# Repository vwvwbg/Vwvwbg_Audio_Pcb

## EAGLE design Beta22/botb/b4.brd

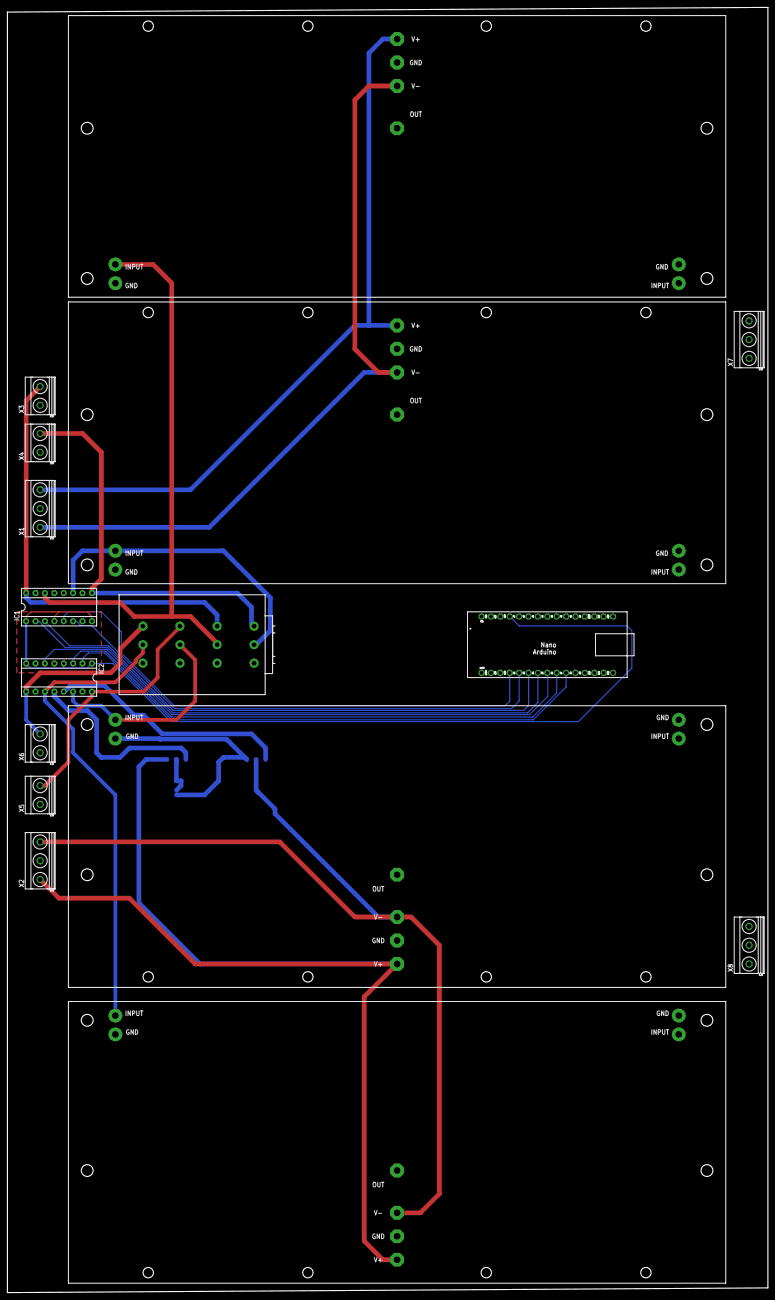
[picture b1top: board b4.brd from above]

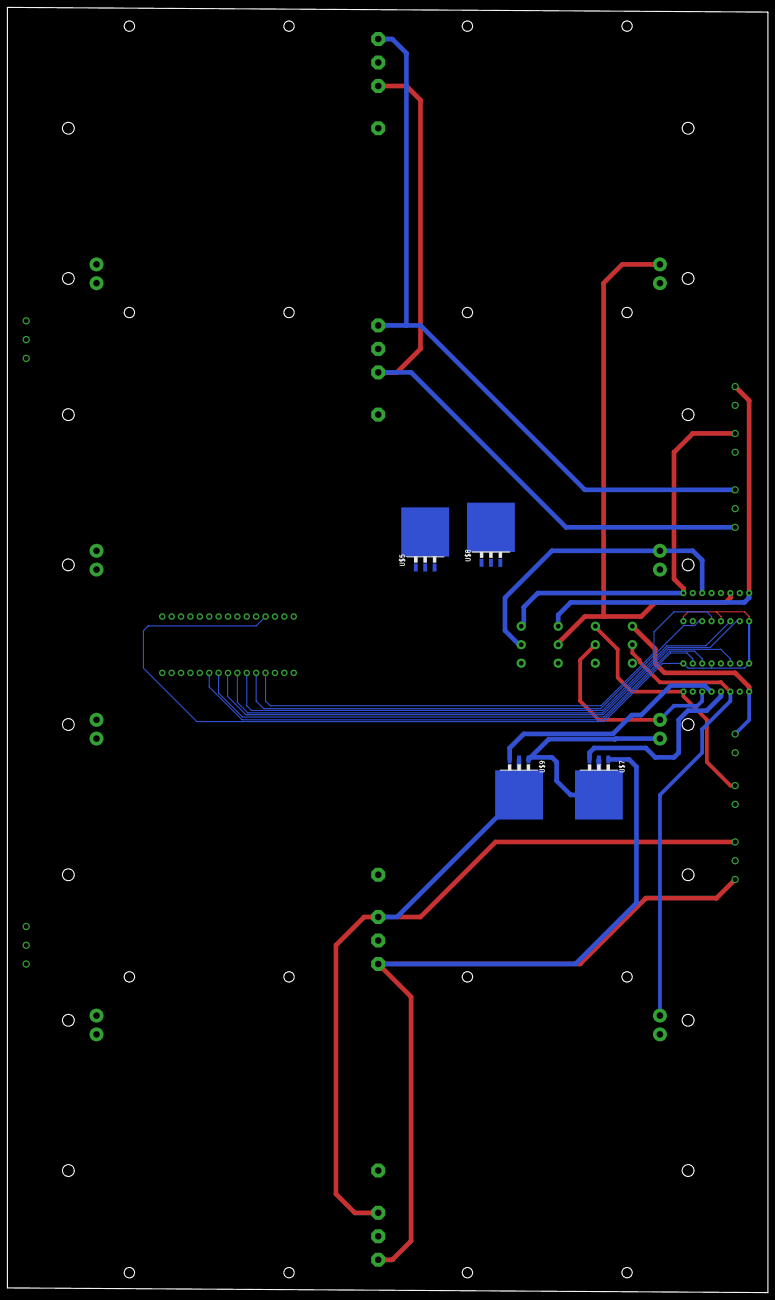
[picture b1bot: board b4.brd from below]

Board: 2 copper layers, 205.7 x 347.6 mm, 20 parts (4 on the bottom side), 25 nets.

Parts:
IC1, IC2: PGA2311P; DIL16
PCB1: ARDUINO_NANO
U$1, U$2, U$3, U$4: B22
U$5, U$7: MC78XX; TO263-3
U$6: ALPSRK274; RK274
U$8, U$9: MC79XX; TO263-3
X1, X2, X7, X8: MKDSN1,5/3-5,08
X3, X4, X5, X6: MKDSN1,5/2-5,08

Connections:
DGND: IC1.5, IC2.5, PCB1.GND
GND: IC1.10, IC1.15, IC2.10, IC2.15, U$1.GND, U$1.GND1, U$1.GND2, U$2.GND, U$2.GND1, U$2.GND2, U$3.GND, U$3.GND1, U$3.GND2, U$4.GND, U$4.GND1, U$4.GND2, U$5.2, U$5.TAB, U$6.G1, U$6.G2, U$6.G3, U$6.G4, U$7.2, U$7.TAB, U$8.1, U$9.1, X1.2, X2.2, X3.1, X5.1, X6.1, X7.2, X8.2
unnamed: U$3.V+, U$4.V+, U$5.1, X1.3, X7.3
unnamed: U$3.V-, U$4.V-, U$8.2, U$8.TAB, X1.1, X7.1
unnamed: IC1.16, U$6.I2, X3.2
unnamed: U$1.V+, U$2.V+, U$7.1, X2.1, X8.1
unnamed: U$1.V-, U$2.V-, U$9.2, U$9.TAB, X2.3, X8.3
unnamed: IC1.14, U$4.IN1, U$6.O2
unnamed: IC1.9, U$6.I1, X4.2
unnamed: IC1.11, U$3.IN1, U$6.O1
unnamed: IC2.14, U$2.IN2, U$6.O3
unnamed: IC2.11, U$1.IN2, U$6.O4
unnamed: IC2.9, U$6.I4, X6.2
unnamed: IC1.2, PCB1.D4
unnamed: IC2.16, U$6.I3, X5.2
unnamed: IC1.3, PCB1.D3
unnamed: IC2.2, PCB1.D7
unnamed: IC2.3, PCB1.D6
unnamed: IC1.1, IC1.4, IC1.8, IC2.1, IC2.4, IC2.8, PCB1.5V
unnamed: IC2.13, U$9.3
unnamed: IC2.6, PCB1.D5
unnamed: IC1.6, PCB1.D2
unnamed: IC2.12, U$7.3
unnamed: IC1.12, U$5.3
unnamed: IC1.13, U$8.3

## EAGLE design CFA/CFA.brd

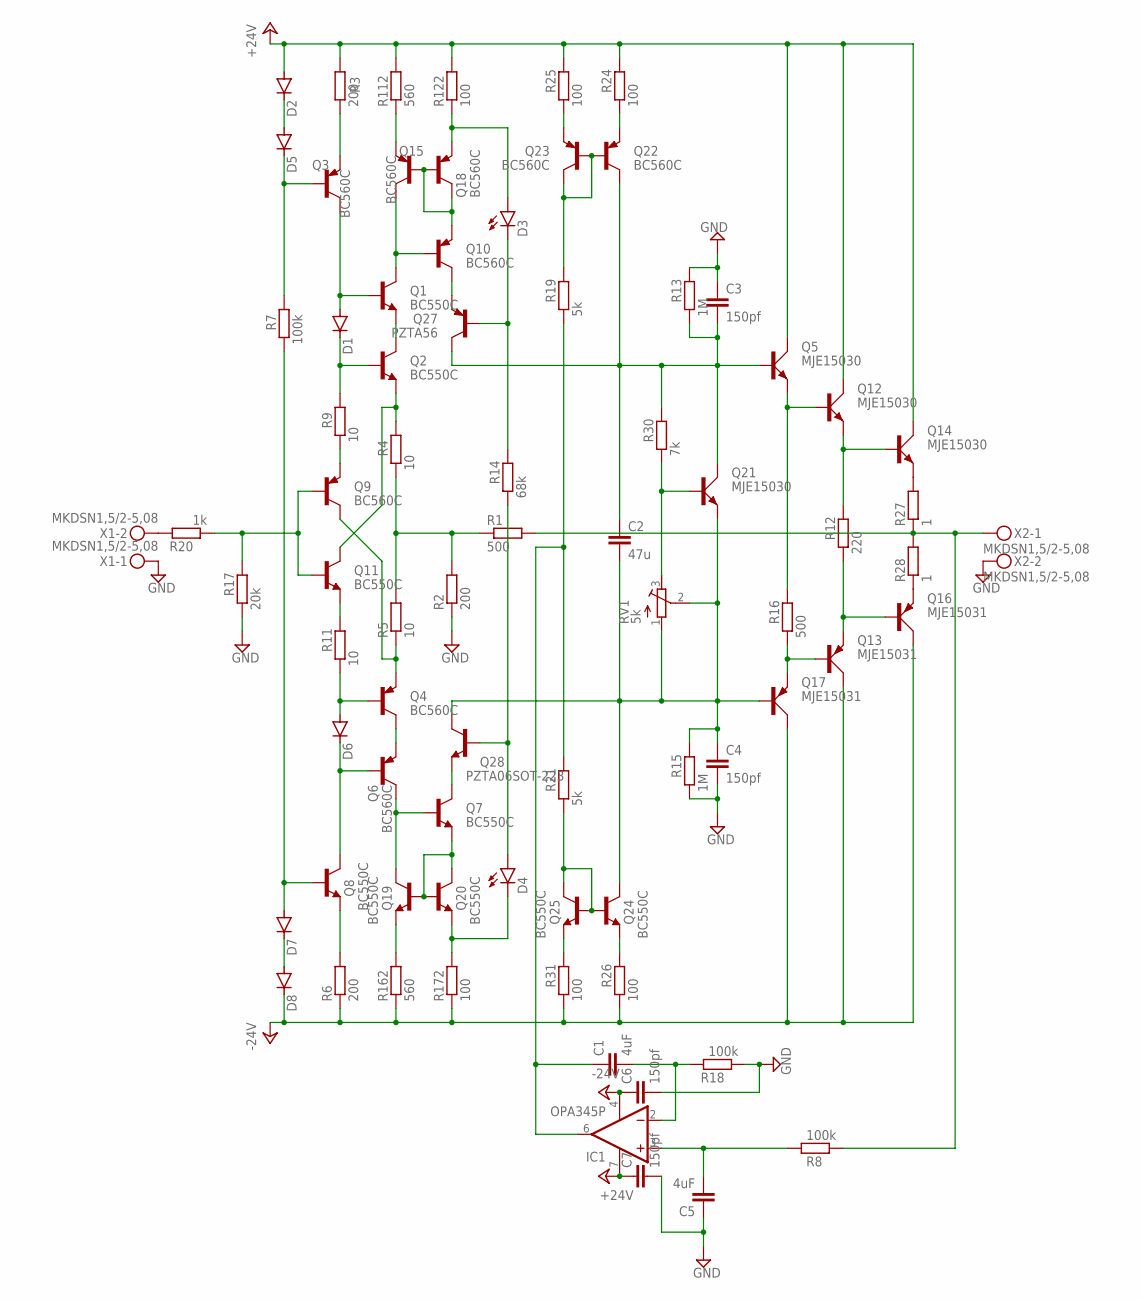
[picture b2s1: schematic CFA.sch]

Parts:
C1, C5: 4uF; C1210
C2: 47u; C1210
C3, C4, C6, C7: 150pf; C0805
D1, D2, D5, D6, D7, D8: DIODE-SOD80C; SOD80C
D3, D4: LED5MM
IC1: OPA345P; DIL08
Q1, Q2, Q7, Q8, Q11, Q19, Q20, Q24, Q25: BC550C; TO92-EBC
Q3, Q4, Q6, Q9, Q10, Q15, Q18, Q22, Q23: BC560C; TO92-EBC
Q5, Q12, Q14, Q21: MJE15030; TO220AV
Q13, Q16, Q17: MJE15031; TO220AV
Q27: PZTA56; SOT223
Q28: PZTA06SOT-223; SOT223
R1, R16: 500; MINI_MELF-0204R
R2, R3, R6: 200; MINI_MELF-0204R
R4, R5, R9, R11: 10; MINI_MELF-0204R
R7, R8, R18: 100k; MINI_MELF-0204R
R12: 220; MINI_MELF-0204R
R13, R15: 1M; MINI_MELF-0204R
R14: 68k; MINI_MELF-0204R
R17: 20k; MINI_MELF-0204R
R19, R21: 5k; MINI_MELF-0204R
R20: 1k; MINI_MELF-0204R
R24, R25, R26, R31, R122, R172: 100; MINI_MELF-0204R
R27, R28: 1; 0617/22
R30: 7k; MINI_MELF-0204R
R112, R162: 560; MINI_MELF-0204R
RV1: 5k; RTRIM3296W
X1, X2: MKDSN1,5/2-5,08

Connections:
+24V: C7.1, D2.A, IC1.7 (V+), Q5.C, Q12.C, Q14.C, R3.2, R24.2, R25.2, R112.2, R122.2
-24V: C6.1, D8.C, IC1.4 (V-), Q13.C, Q16.C, Q17.C, R6.1, R26.1, R31.1, R162.1, R172.1
GND: C3.1, C4.2, C5.1, C6.2, C7.2, R2.1, R13.2, R15.1, R17.1, R18.1, X1.1, X2.2
unnamed: Q21.B, R30.1, RV1.3 (E)
unnamed: Q3.E, R3.1
unnamed: D1.A, Q1.B, Q3.C
unnamed: D2.C, D5.A
unnamed: D5.C, Q3.B, R7.2
unnamed: D1.C, Q2.B, R9.2
unnamed: Q1.E, Q2.C
unnamed: Q2.E, Q11.C, R4.2
unnamed: R1.1, R2.2, R4.1, R5.2
unnamed: Q4.E, Q9.C, R5.1
unnamed: Q4.C, Q6.E
unnamed: D6.A, Q4.B, R11.1
unnamed: D6.C, Q6.B, Q8.C
unnamed: Q8.E, R6.2
unnamed: D7.A, Q8.B, R7.1
unnamed: D7.C, D8.A
unnamed: R20.2, X1.2
unnamed: Q9.E, R9.1
unnamed: Q11.E, R11.2
unnamed: Q15.E, R112.1
unnamed: Q9.B, Q11.B, R17.2, R20.1
unnamed: Q1.C, Q10.B, Q15.C
unnamed: Q10.E, Q15.B, Q18.B, Q18.C
unnamed: D3.A, Q18.E, R122.1
unnamed: Q10.C, Q27.3 (E)
unnamed: D3.K (C), Q27.1 (B), R14.2
unnamed: Q7.E, Q19.B, Q20.B, Q20.C
unnamed: D4.K (C), Q20.E, R172.2
unnamed: Q19.E, R162.2
unnamed: Q6.C, Q7.B, Q19.C
unnamed: Q7.C, Q28.3 (E)
unnamed: D4.A, Q28.1 (B), R14.1
unnamed: Q12.E, Q14.B, R12.2
unnamed: C2.1, C3.2, Q5.B, Q21.C, Q22.C, Q27.2 (C), Q27.4 (C), R13.1, R30.2
unnamed: Q22.B, Q23.B, Q23.C, R19.2
unnamed: Q24.B, Q25.B, Q25.C, R21.1
unnamed: Q23.E, R25.1
unnamed: Q22.E, R24.1
unnamed: C1.1, IC1.6 (OUT), R19.1, R21.2
unnamed: R1.2, R8.1, R27.1, R28.2, X2.1
unnamed: Q25.E, R31.2
unnamed: Q24.E, R26.2
unnamed: Q5.E, Q12.B, R16.2
unnamed: Q13.B, Q17.E, R16.1
unnamed: C2.2, C4.1, Q17.B, Q21.E, Q24.C, Q28.2 (C), Q28.4 (C), R15.2, RV1.1 (A), RV1.2 (S)
unnamed: Q13.E, Q16.B, R12.1
unnamed: Q14.E, R27.2
unnamed: Q16.E, R28.1
unnamed: C1.2, IC1.2 (-IN), R18.2
unnamed: C5.2, IC1.3 (+IN), R8.2

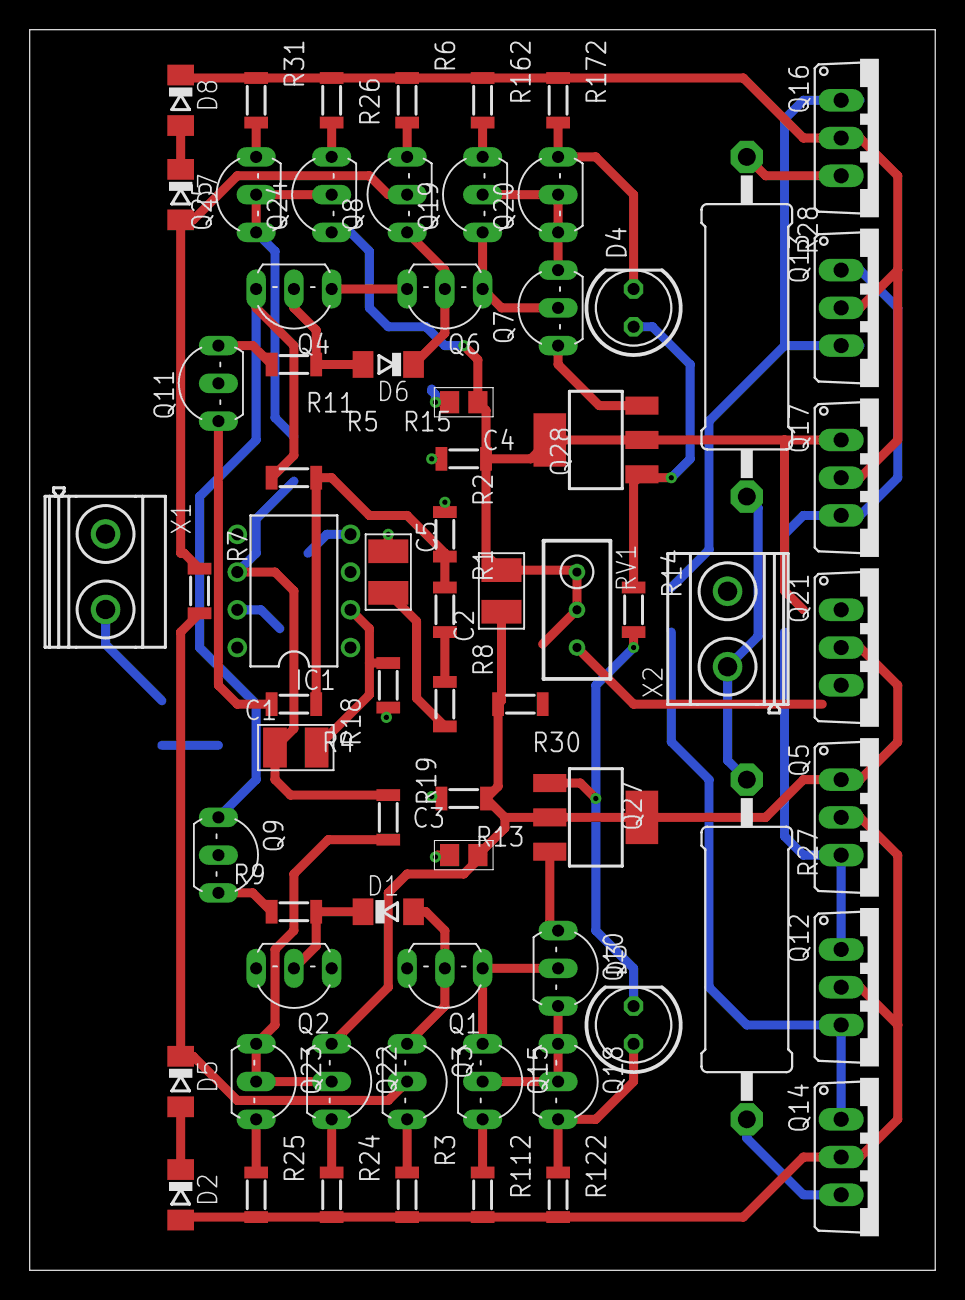
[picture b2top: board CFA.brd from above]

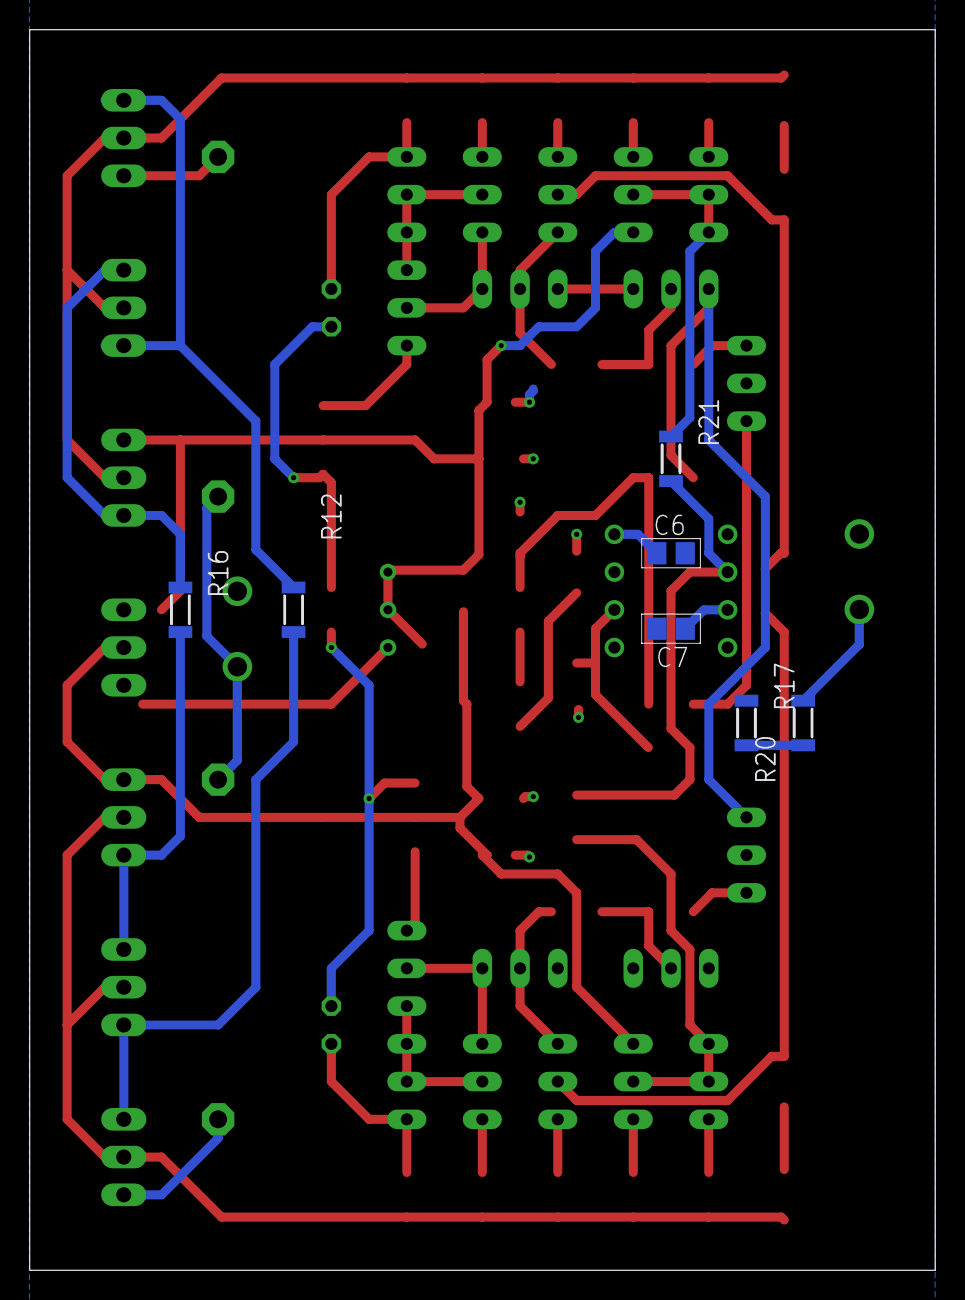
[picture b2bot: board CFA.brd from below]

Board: 2 copper layers, 60.9 x 83.5 mm, 77 parts (7 on the bottom side), 53 nets.

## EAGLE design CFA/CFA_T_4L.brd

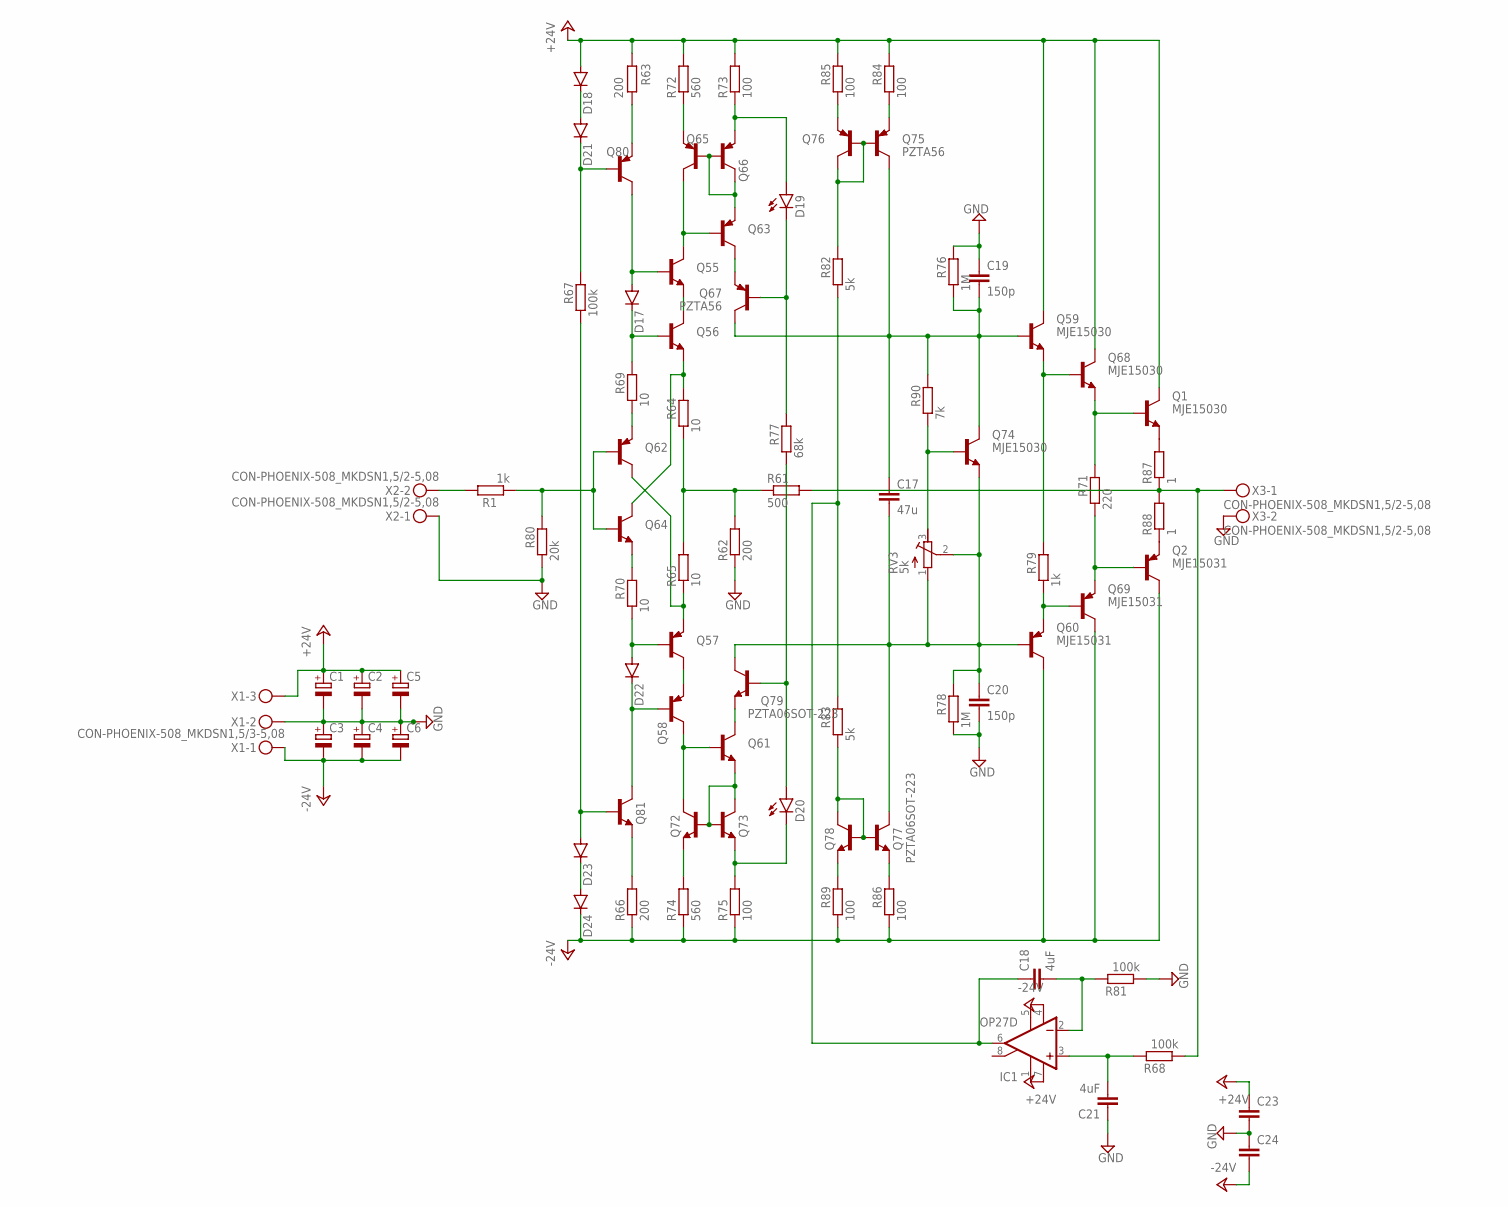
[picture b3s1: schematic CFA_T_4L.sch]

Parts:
C1, C2, C3, C4, C5, C6: CPOL-EUE3.5-8; E3,5-8
C17: 47u; C1210
C18, C21: 4uF; C1210
C19, C20: 150p; C0805
C23, C24: C-EUC0603K; C0603K
D17, D18, D21, D22, D23, D24: DIODE-SOD80C; SOD80C
D19, D20: LED3MM
IC1: OP27D; SO08
Q1, Q59, Q68, Q74: MJE15030; TRANSISTOR_TO220KG
Q2, Q60, Q69: MJE15031; TRANSISTOR_TO220KG
Q55, Q56, Q64, Q72, Q73, Q78, Q81: TRANSISTOR_BC850-NPN-SOT23-BEC; TRANSISTOR_SOT23-BEC
Q57, Q58, Q62, Q63, Q65, Q66, Q76, Q80: TRANSISTOR_BC857C-PNP-SOT23-BEC; TRANSISTOR_SOT23-BEC
Q61: TRANSISTOR_BC847-NPN-SOT23-BEC; TRANSISTOR_SOT23-BEC
Q67, Q75: PZTA56; SOT223
Q77, Q79: PZTA06SOT-223; SOT223
R1, R79: 1k; MINI_MELF-0204W
R61: 500; MINI_MELF-0204W
R62, R63, R66: 200; MINI_MELF-0204W
R64, R65, R69, R70: 10; MINI_MELF-0204W
R67, R68, R81: 100k; MINI_MELF-0204W
R71: 220; MINI_MELF-0204W
R72, R74: 560; MINI_MELF-0204W
R73, R75, R84, R85, R86, R89: 100; MINI_MELF-0204W
R76, R78: 1M; MINI_MELF-0204W
R77: 68k; MINI_MELF-0204W
R80: 20k; MINI_MELF-0204W
R82, R83: 5k; MINI_MELF-0204W
R87, R88: 1; TO220-2
R90: 7k; MINI_MELF-0204W
RV3: 5k; RTRIM3296W
X1: CON-PHOENIX-508_MKDSN1,5/3-5,08
X2, X3: CON-PHOENIX-508_MKDSN1,5/2-5,08

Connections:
+24V: C1.+, C2.+, C5.+, C23.1, D18.A, IC1.7 (V+), Q1.2 (C), Q59.2 (C), Q68.2 (C), R63.2, R72.2, R73.2, R84.2, R85.2, X1.3
-24V: C3.-, C4.-, C6.-, C24.2, D24.C, IC1.4 (V-), Q2.2 (C), Q60.2 (C), Q69.2 (C), R66.1, R74.1, R75.1, R86.1, R89.1, X1.1
GND: C1.-, C2.-, C3.+, C4.+, C5.-, C6.+, C19.1, C20.2, C21.1, C23.2, C24.1, R62.1, R76.2, R78.1, R80.1, R81.1, X1.2, X2.1, X3.2
unnamed: C17.2, C20.1, Q60.1 (B), Q74.3 (E), Q77.2 (C), Q77.4 (C), Q79.2 (C), Q79.4 (C), R78.2, RV3.1 (A), RV3.2 (S)
unnamed: Q74.1 (B), R90.1, RV3.3 (E)
unnamed: R1.2, X2.2
unnamed: Q1.3 (E), R87.2
unnamed: Q2.3 (E), R88.1
unnamed: Q80.E, R63.1
unnamed: D17.A, Q55.B, Q80.C
unnamed: D18.C, D21.A
unnamed: D21.C, Q80.B, R67.2
unnamed: D17.C, Q56.B, R69.2
unnamed: Q55.E, Q56.C
unnamed: Q56.E, Q64.C, R64.2
unnamed: R61.1, R62.2, R64.1, R65.2
unnamed: Q57.E, Q62.C, R65.1
unnamed: D22.A, Q57.B, R70.1
unnamed: D22.C, Q58.B, Q81.C
unnamed: Q81.E, R66.2
unnamed: D23.C, D24.A
unnamed: Q57.C, Q58.E
unnamed: Q62.E, R69.1
unnamed: Q64.E, R70.2
unnamed: Q62.B, Q64.B, R1.1, R80.2
unnamed: Q55.C, Q63.B, Q65.C
unnamed: Q63.E, Q65.B, Q66.B, Q66.C
unnamed: Q65.E, R72.1
unnamed: D19.A, Q66.E, R73.1
unnamed: Q63.C, Q67.3 (E)
unnamed: D19.K (C), Q67.1 (B), R77.2
unnamed: Q61.E, Q72.B, Q73.B, Q73.C
unnamed: D20.K (C), Q73.E, R75.2
unnamed: Q72.E, R74.2
unnamed: Q58.C, Q61.B, Q72.C
unnamed: Q61.C, Q79.3 (E)
unnamed: D20.A, Q79.1 (B), R77.1
unnamed: C17.1, C19.2, Q59.1 (B), Q67.2 (C), Q67.4 (C), Q74.2 (C), Q75.2 (C), Q75.4 (C), R76.1, R90.2
unnamed: Q75.1 (B), Q76.B, Q76.C, R82.2
unnamed: Q77.1 (B), Q78.B, Q78.C, R83.1
unnamed: Q76.E, R85.1
unnamed: Q75.3 (E), R84.1
unnamed: R61.2, R68.1, R87.1, R88.2, X3.1
unnamed: Q78.E, R89.2
unnamed: Q77.3 (E), R86.2
unnamed: Q59.3 (E), Q68.1 (B), R79.2
unnamed: Q60.3 (E), Q69.1 (B), R79.1
unnamed: Q1.1 (B), Q68.3 (E), R71.2
unnamed: Q2.1 (B), Q69.3 (E), R71.1
unnamed: C18.2, IC1.2 (-IN), R81.2
unnamed: C21.2, IC1.3 (+IN), R68.2
unnamed: D23.A, Q81.B, R67.1
unnamed: C18.1, IC1.6 (OUT), R82.1, R83.2

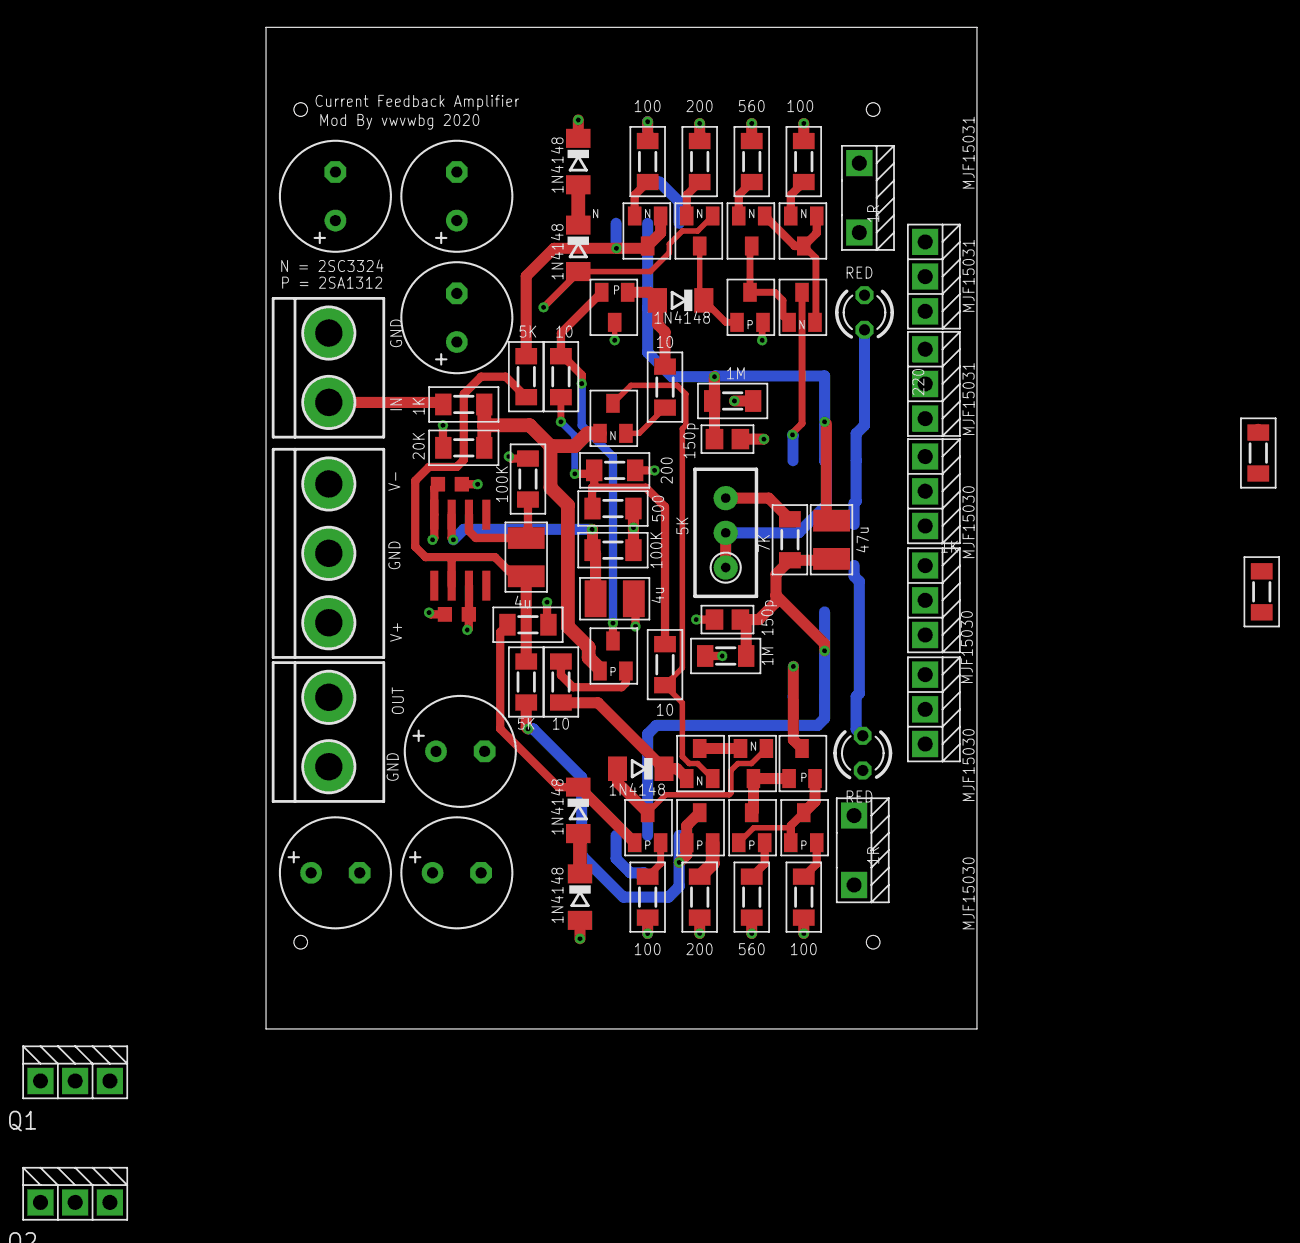
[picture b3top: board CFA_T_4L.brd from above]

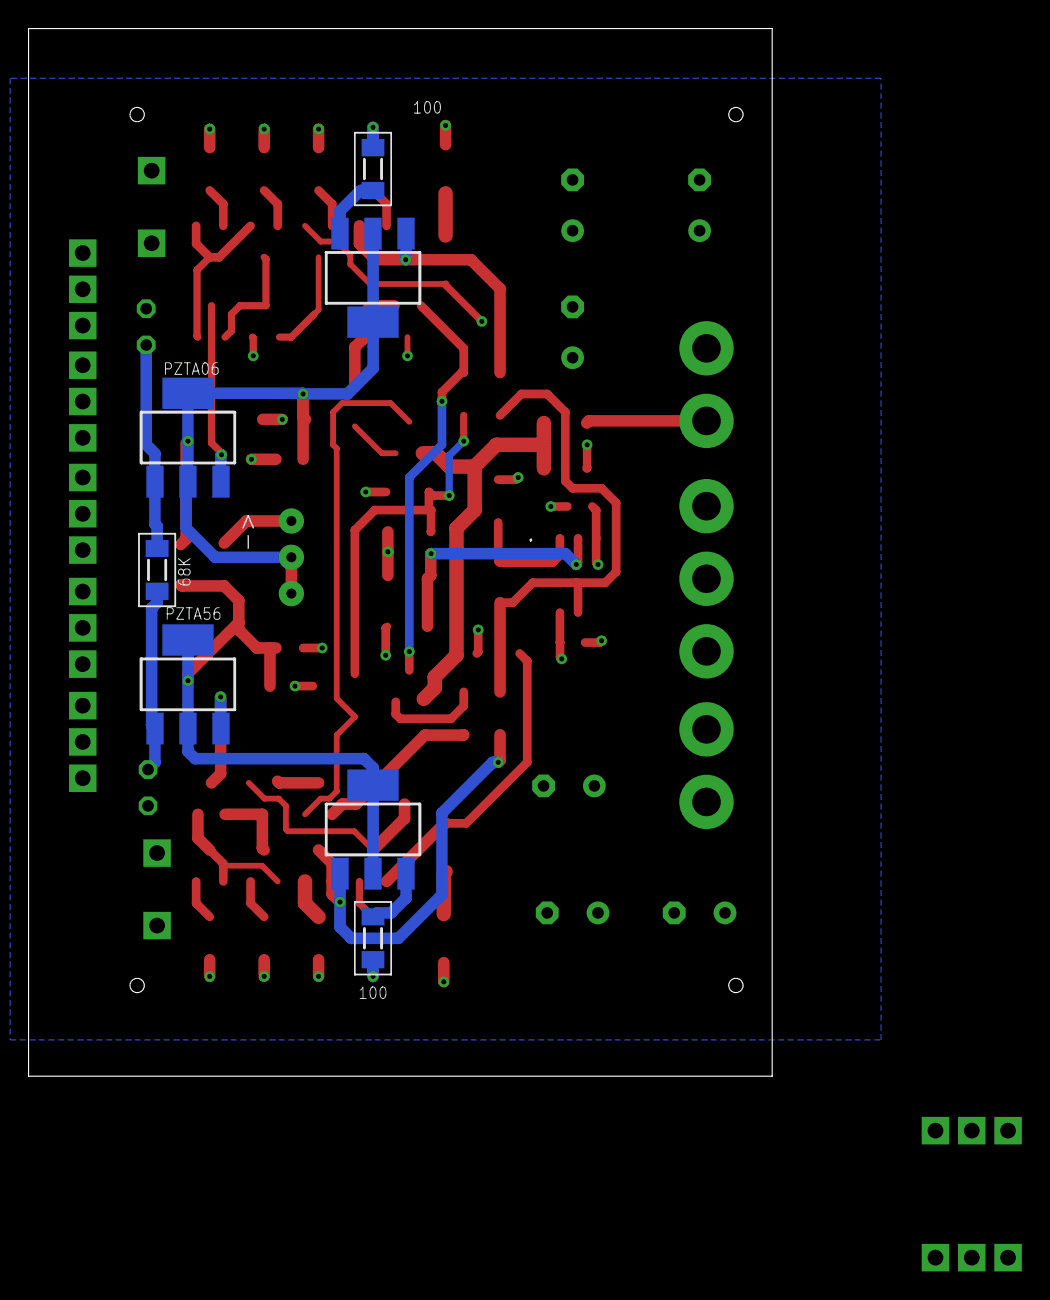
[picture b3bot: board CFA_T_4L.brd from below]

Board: 4 copper layers, 52.0 x 73.3 mm, 84 parts (7 on the bottom side), 53 nets.

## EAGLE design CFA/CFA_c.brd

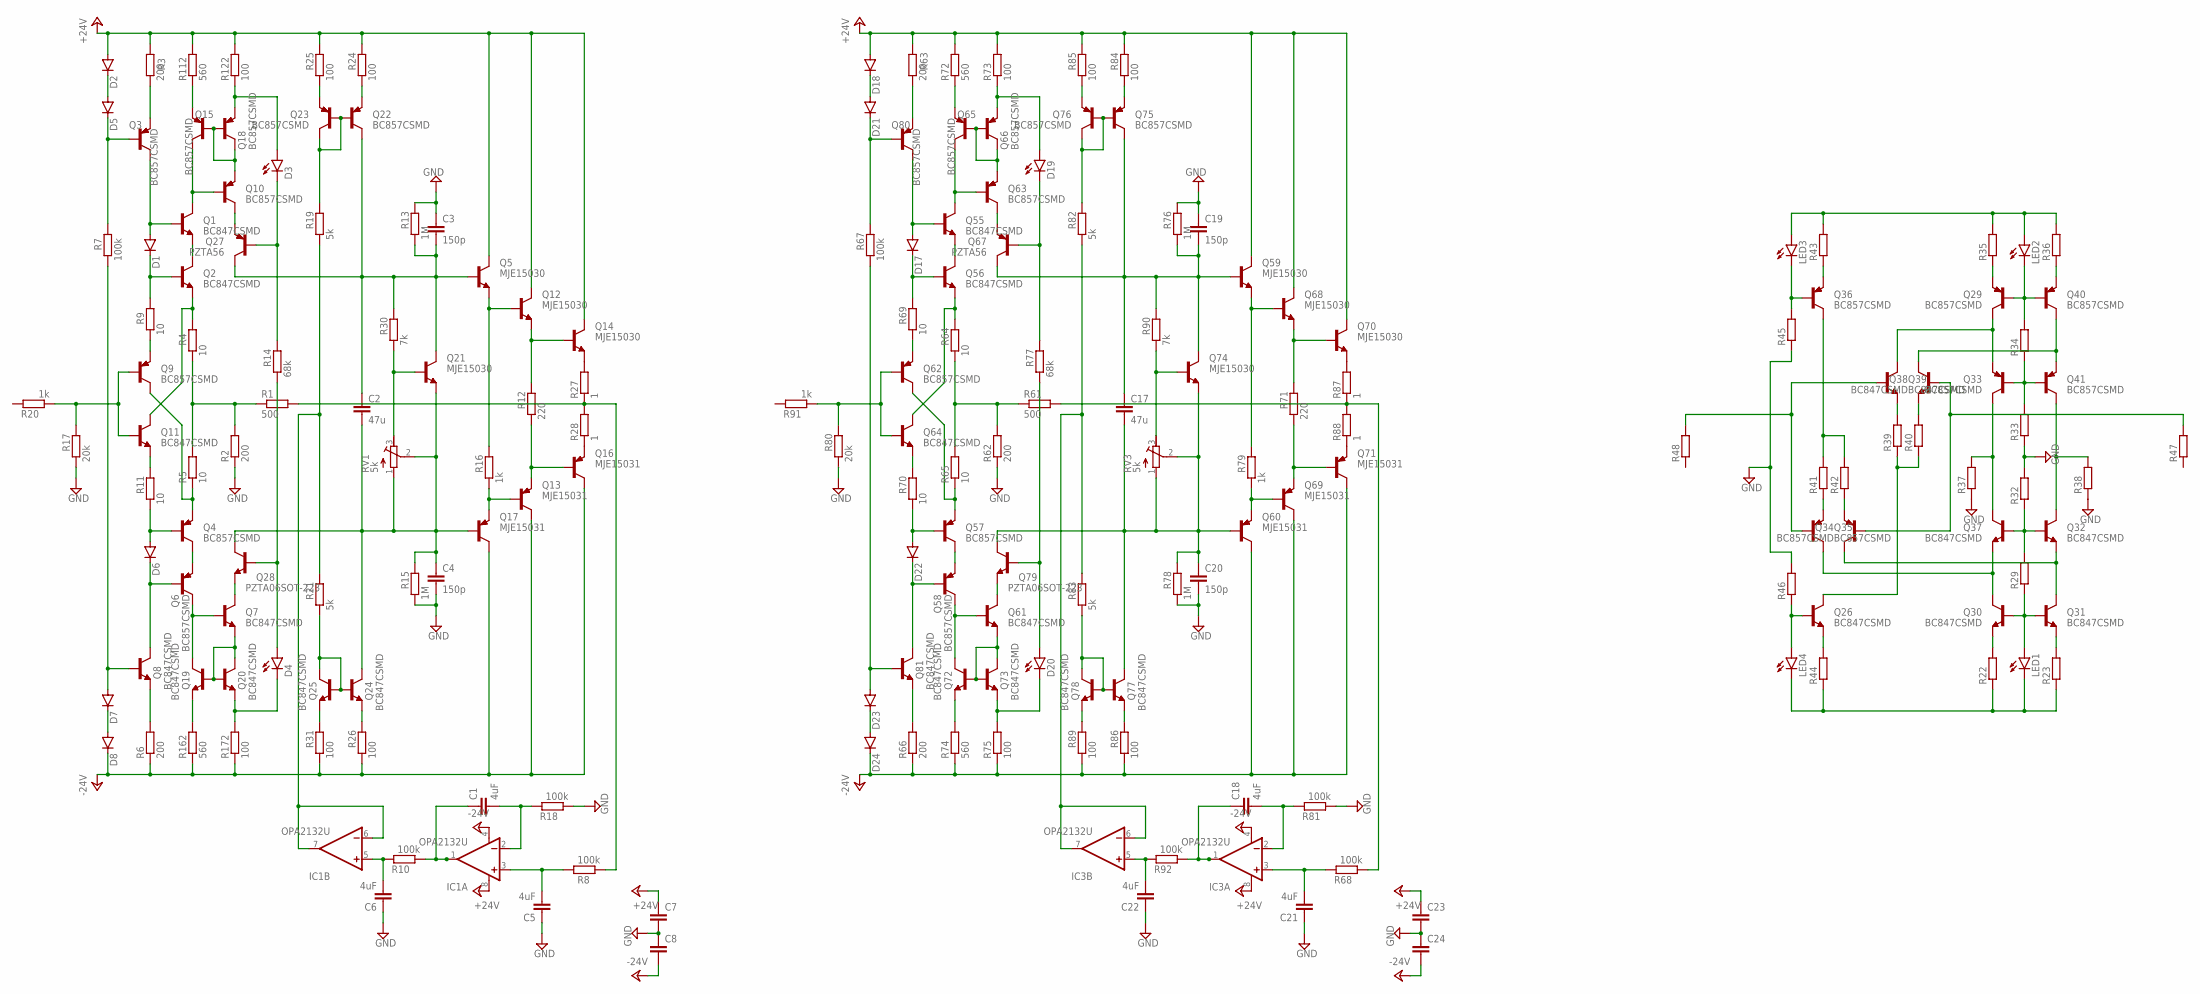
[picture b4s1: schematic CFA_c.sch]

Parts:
C1, C5, C6, C18, C21, C22: 4uF; C1210
C2, C17: 47u; C1210
C3, C4, C19, C20: 150p; C0805
C7, C8, C23, C24: C-EUC0603K; C0603K
D1, D2, D5, D6, D7, D8, D17, D18, D21, D22, D23, D24: DIODE-SOD80C; SOD80C
D3, D4, D19, D20: LEDCHIPLED_1206; CHIPLED_1206
IC1, IC3: OPA2132U; SO08
LED1, LED2, LED3, LED4: LEDCHIPLED_1206; CHIPLED_1206
Q1, Q2, Q7, Q8, Q11, Q19, Q20, Q24, Q25, Q26, Q30, Q31, Q32, Q37, Q38, Q39, Q55, Q56, Q61, Q64, Q72, Q73, Q77, Q78, Q81: BC847CSMD; SOT23
Q3, Q4, Q6, Q9, Q10, Q15, Q18, Q22, Q23, Q29, Q33, Q34, Q35, Q36, Q40, Q41, Q57, Q58, Q62, Q63, Q65, Q66, Q75, Q76, Q80: BC857CSMD; SOT23-BEC
Q5, Q12, Q14, Q21, Q59, Q68, Q70, Q74: MJE15030; DPAK
Q13, Q16, Q17, Q60, Q69, Q71: MJE15031; DPAK
Q27, Q67: PZTA56; SOT223
Q28, Q79: PZTA06SOT-223; SOT223
R1, R61: 500; MINI_MELF-0204W
R2, R3, R6, R62, R63, R66: 200; MINI_MELF-0204W
R4, R5, R9, R11, R64, R65, R69, R70: 10; MINI_MELF-0204W
R7, R8, R10, R18, R67, R68, R81, R92: 100k; MINI_MELF-0204W
R12, R71: 220; MINI_MELF-0204W
R13, R15, R76, R78: 1M; MINI_MELF-0204W
R14, R77: 68k; MINI_MELF-0204W
R16, R20, R79, R91: 1k; MINI_MELF-0204W
R17, R80: 20k; MINI_MELF-0204W
R19, R21, R82, R83: 5k; MINI_MELF-0204W
R22, R23, R29, R32, R33, R34, R35, R36, R37, R38, R39, R40, R41, R42, R43, R44, R45, R46, R47, R48: R-EU_MELF0204W; MINI_MELF-0204W
R24, R25, R26, R31, R73, R75, R84, R85, R86, R89, R122, R172: 100; MINI_MELF-0204W
R27, R28, R87, R88: 1; R4527
R30, R90: 7k; MINI_MELF-0204W
R72, R74, R112, R162: 560; MINI_MELF-0204W
RV1, RV3: 5k; RTRIMTS63Y

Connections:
+24V: C7.1, C23.1, D2.A, D18.A, IC1.8 (V+), IC3.8 (V+), Q5.4 (C), Q12.4 (C), Q14.4 (C), Q59.4 (C), Q68.4 (C), Q70.4 (C), R3.2, R24.2, R25.2, R63.2, R72.2, R73.2, R84.2, R85.2, R112.2, R122.2
-24V: C8.2, C24.2, D8.C, D24.C, IC1.4 (V-), IC3.4 (V-), Q13.4 (C), Q16.4 (C), Q17.4 (C), Q60.4 (C), Q69.4 (C), Q71.4 (C), R6.1, R26.1, R31.1, R66.1, R74.1, R75.1, R86.1, R89.1, R162.1, R172.1
GND: C3.1, C4.2, C5.1, C6.1, C7.2, C8.1, C19.1, C20.2, C21.1, C22.1, C23.2, C24.1, R2.1, R13.2, R15.1, R17.1, R18.1, R32.2, R33.1, R37.1, R38.1, R45.1, R46.2, R62.1, R76.2, R78.1, R80.1, R81.1
unnamed: Q21.1 (B), R30.1, RV1.3 (E)
unnamed: Q3.E, R3.1
unnamed: D1.A, Q1.1 (B), Q3.C
unnamed: D2.C, D5.A
unnamed: D5.C, Q3.B, R7.2
unnamed: D1.C, Q2.1 (B), R9.2
unnamed: Q1.2 (E), Q2.3 (C)
unnamed: Q2.2 (E), Q11.3 (C), R4.2
unnamed: R1.1, R2.2, R4.1, R5.2
unnamed: Q4.E, Q9.C, R5.1
unnamed: Q4.C, Q6.E
unnamed: D6.A, Q4.B, R11.1
unnamed: D6.C, Q6.B, Q8.3 (C)
unnamed: Q8.2 (E), R6.2
unnamed: D7.A, Q8.1 (B), R7.1
unnamed: D7.C, D8.A
unnamed: C1.1, IC1.1 (OUT), R10.1
unnamed: C6.2, IC1.5 (+IN), R10.2
unnamed: Q9.E, R9.1
unnamed: Q11.2 (E), R11.2
unnamed: Q15.E, R112.1
unnamed: Q9.B, Q11.1 (B), R17.2, R20.1
unnamed: Q1.3 (C), Q10.B, Q15.C
unnamed: Q10.E, Q15.B, Q18.B, Q18.C
unnamed: D3.A, Q18.E, R122.1
unnamed: Q10.C, Q27.3 (E)
unnamed: D3.C, Q27.1 (B), R14.2
unnamed: Q7.2 (E), Q19.1 (B), Q20.1 (B), Q20.3 (C)
unnamed: D4.C, Q20.2 (E), R172.2
unnamed: Q19.2 (E), R162.2
unnamed: Q6.C, Q7.1 (B), Q19.3 (C)
unnamed: Q7.3 (C), Q28.3 (E)
unnamed: D4.A, Q28.1 (B), R14.1
unnamed: Q12.3 (E), Q14.1 (B), R12.2
unnamed: C2.1, C3.2, Q5.1 (B), Q21.4 (C), Q22.C, Q27.2 (C), Q27.4 (C), R13.1, R30.2
unnamed: Q22.B, Q23.B, Q23.C, R19.2
unnamed: Q24.1 (B), Q25.1 (B), Q25.3 (C), R21.1
unnamed: Q23.E, R25.1
unnamed: Q22.E, R24.1
unnamed: IC1.6 (-IN), IC1.7 (OUT), R19.1, R21.2
unnamed: R1.2, R8.1, R27.1, R28.2
unnamed: Q25.2 (E), R31.2
unnamed: Q24.2 (E), R26.2
unnamed: Q5.3 (E), Q12.1 (B), R16.2
unnamed: Q13.1 (B), Q17.3 (E), R16.1
unnamed: C2.2, C4.1, Q17.1 (B), Q21.3 (E), Q24.3 (C), Q28.2 (C), Q28.4 (C), R15.2, RV1.1 (A), RV1.2 (S)
unnamed: Q13.3 (E), Q16.1 (B), R12.1
unnamed: Q14.3 (E), R27.2
unnamed: Q16.3 (E), R28.1
unnamed: C1.2, IC1.2 (-IN), R18.2
unnamed: C5.2, IC1.3 (+IN), R8.2
unnamed: LED1.C, LED4.C, R22.1, R23.1, R44.1
unnamed: Q30.2 (E), R22.2
unnamed: Q31.2 (E), R23.2
unnamed: Q31.3 (C), Q32.2 (E), Q34.C
unnamed: Q30.3 (C), Q35.C, Q37.2 (E)
unnamed: LED1.A, Q30.1 (B), Q31.1 (B), R29.1
unnamed: Q32.1 (B), Q37.1 (B), R29.2, R32.1
unnamed: Q33.C, Q37.3 (C), R37.2
unnamed: Q32.3 (C), Q41.C, R38.2
unnamed: Q33.B, Q41.B, R33.2, R34.1
unnamed: Q29.C, Q33.E, Q39.3 (C)
unnamed: LED2.C, Q29.B, Q40.B, R34.2
unnamed: Q38.3 (C), Q40.C, Q41.E
unnamed: Q29.E, R35.1
unnamed: Q40.E, R36.1
unnamed: LED2.A, LED3.A, R35.2, R36.2, R43.2
unnamed: LED3.C, Q36.B, R45.2
unnamed: Q36.E, R43.1
unnamed: Q36.C, R41.2, R42.2
unnamed: Q34.E, R42.1
unnamed: Q35.E, R41.1
unnamed: Q34.B, Q38.1 (B), R47.2
unnamed: Q35.B, Q39.1 (B), R48.2
unnamed: Q39.2 (E), R39.2
unnamed: Q38.2 (E), R40.2
unnamed: Q26.3 (C), R39.1, R40.1
unnamed: Q26.2 (E), R44.2
unnamed: LED4.A, Q26.1 (B), R46.1
unnamed: Q74.1 (B), R90.1, RV3.3 (E)
unnamed: Q80.E, R63.1
unnamed: D17.A, Q55.1 (B), Q80.C
unnamed: D18.C, D21.A
unnamed: D21.C, Q80.B, R67.2
unnamed: D17.C, Q56.1 (B), R69.2
unnamed: Q55.2 (E), Q56.3 (C)
unnamed: Q56.2 (E), Q64.3 (C), R64.2
unnamed: R61.1, R62.2, R64.1, R65.2
unnamed: Q57.E, Q62.C, R65.1
unnamed: D22.A, Q57.B, R70.1
unnamed: D22.C, Q58.B, Q81.3 (C)
unnamed: Q81.2 (E), R66.2
unnamed: D23.C, D24.A
unnamed: Q57.C, Q58.E
unnamed: Q62.E, R69.1
unnamed: Q64.2 (E), R70.2
unnamed: Q62.B, Q64.1 (B), R80.2, R91.1
unnamed: Q55.3 (C), Q63.B, Q65.C
unnamed: Q63.E, Q65.B, Q66.B, Q66.C
unnamed: Q65.E, R72.1
unnamed: D19.A, Q66.E, R73.1
unnamed: Q63.C, Q67.3 (E)
unnamed: D19.C, Q67.1 (B), R77.2
unnamed: Q61.2 (E), Q72.1 (B), Q73.1 (B), Q73.3 (C)
unnamed: D20.C, Q73.2 (E), R75.2
unnamed: Q72.2 (E), R74.2
unnamed: Q58.C, Q61.1 (B), Q72.3 (C)
unnamed: Q61.3 (C), Q79.3 (E)
unnamed: D20.A, Q79.1 (B), R77.1
unnamed: C17.1, C19.2, Q59.1 (B), Q67.2 (C), Q67.4 (C), Q74.4 (C), Q75.C, R76.1, R90.2
unnamed: Q75.B, Q76.B, Q76.C, R82.2
unnamed: Q77.1 (B), Q78.1 (B), Q78.3 (C), R83.1
unnamed: Q76.E, R85.1
unnamed: Q75.E, R84.1
unnamed: IC3.6 (-IN), IC3.7 (OUT), R82.1, R83.2
unnamed: R61.2, R68.1, R87.1, R88.2
unnamed: Q78.2 (E), R89.2
unnamed: Q77.2 (E), R86.2
unnamed: Q59.3 (E), Q68.1 (B), R79.2
unnamed: Q60.3 (E), Q69.1 (B), R79.1
unnamed: C17.2, C20.1, Q60.1 (B), Q74.3 (E), Q77.3 (C), Q79.2 (C), Q79.4 (C), R78.2, RV3.1 (A), RV3.2 (S)
unnamed: Q68.3 (E), Q70.1 (B), R71.2
unnamed: Q69.3 (E), Q71.1 (B), R71.1
unnamed: Q70.3 (E), R87.2
unnamed: Q71.3 (E), R88.1
unnamed: C18.2, IC3.2 (-IN), R81.2
unnamed: C21.2, IC3.3 (+IN), R68.2
unnamed: D23.A, Q81.1 (B), R67.1
unnamed: C18.1, IC3.1 (OUT), R92.1
unnamed: C22.2, IC3.5 (+IN), R92.2

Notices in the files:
parts and their libraries:
SparkFun-Connectors: Licensing: Creative Commons ShareAlike 4.0 International - https://creativecommons.org/licenses/by-sa/4.0
